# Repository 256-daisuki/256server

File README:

# 256server

### Welcome to 2^8 Server!! 👋
Here is the repository of the server operated by @256_daisuki.

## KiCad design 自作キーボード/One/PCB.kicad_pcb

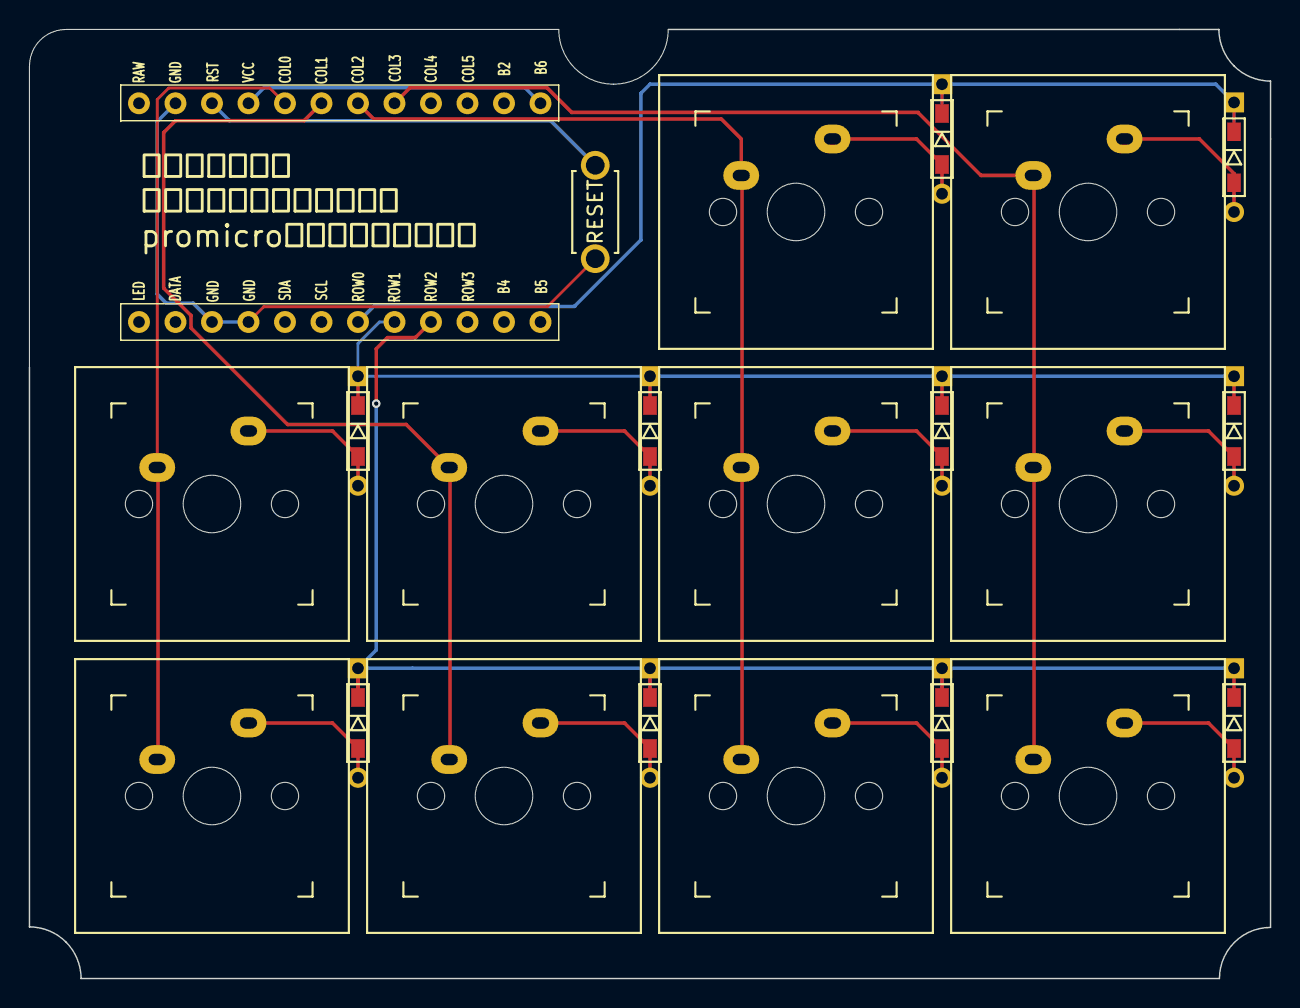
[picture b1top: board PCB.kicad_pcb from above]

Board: 2 copper layers, 86.4 x 66.0 mm, 22 parts (1 on the bottom side), 19 nets.

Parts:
D1, D2, D3, D4, D5, D6, D7, D8, D9, D10: D; D3_TH_SMD
SW1, SW2, SW3, SW4, SW5, SW6, SW7, SW8, SW9, SW10: SW_Push; CherryMX_1u
SW11: SW_Push; ResetSW_1side
U1: Micon_BLEMicroPro; ProMicro_v2_1side

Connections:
Col0: SW3.1, SW7.1, U1.20 (F4/PIN20)
Col1: SW4.1, SW8.1, U1.19 (F5/PIN19)
Col2: SW1.1, SW5.1, SW9.1, U1.18 (F6/PIN18)
Col3: SW2.1, SW6.1, SW10.1, U1.17 (F7/PIN17)
GND: SW11.2, U1.3 (GND), U1.4 (GND), U1.23 (GND)
unnamed: D1.2 (A), SW1.2
unnamed: D2.2 (A), SW2.2
unnamed: D3.2 (A), SW3.2
unnamed: D4.2 (A), SW4.2
unnamed: D5.2 (A), SW5.2
unnamed: D6.2 (A), SW6.2
unnamed: D7.2 (A), SW7.2
unnamed: D8.2 (A), SW8.2
unnamed: D9.2 (A), SW9.2
unnamed: D10.2 (A), SW10.2
Reset: SW11.1, U1.22 (RST)
Row0: D1.1 (K), D2.1 (K), U1.7 (D4/PIN7)
Row1: D3.1 (K), D4.1 (K), D5.1 (K), D6.1 (K), U1.8 (C6/PIN8)
Row2: D7.1 (K), D8.1 (K), D9.1 (K), D10.1 (K), U1.9 (D7/PIN9)

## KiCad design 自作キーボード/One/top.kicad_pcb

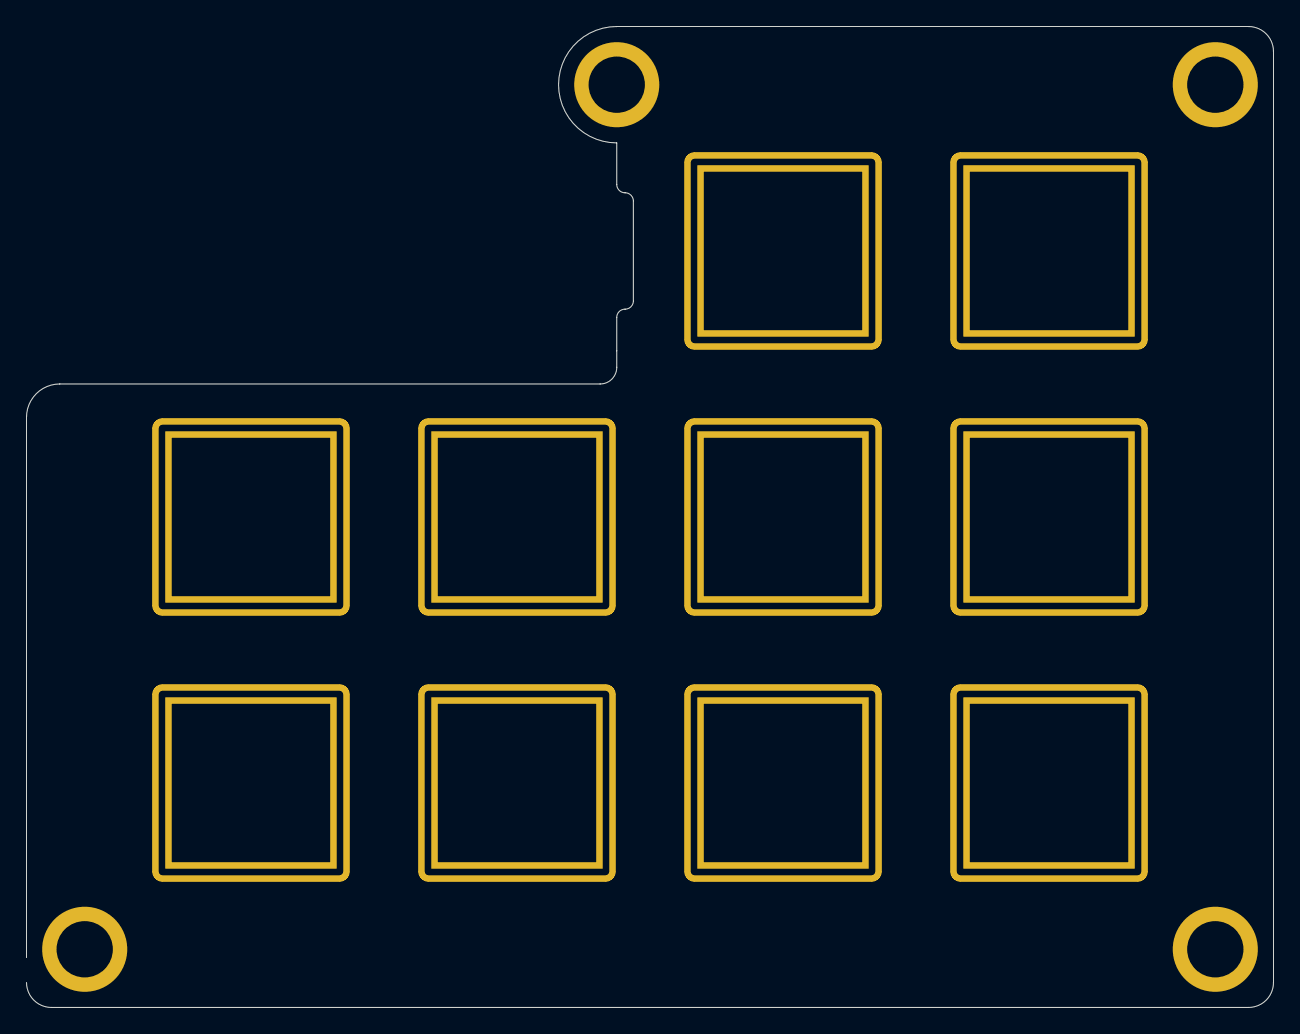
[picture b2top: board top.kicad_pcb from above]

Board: 2 copper layers, 95.3 x 74.9 mm, 14 parts (0 on the bottom side), 4 nets, no tracks yet.

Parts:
Ref**: Val**; M2_HOLE
Ref**#2, Ref**#3, Ref**#4: Val**; M2_HOLE
SW1, SW2, SW3, SW4, SW5, SW6, SW7, SW8, SW9, SW10: SW_Push; SW_Hole_TH

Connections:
Col0: SW3.1, SW7.1
Col1: SW4.1, SW8.1
Col2: SW1.1, SW5.1, SW9.1
Col3: SW2.1, SW6.1, SW10.1

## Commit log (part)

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2023-02-21 やっとシステム構築できたぁ！！！！！！！！！！！！！！！！！！
2023-02-22 どんべい
2023-02-22 ファイル移動
2023-02-23 うぇーい
2023-02-23 結構頑張ってる
2023-02-23 inaoepyikaeo
2023-02-23 色々修正
2023-02-23 banner解禁
2023-02-23 今日はもう終わり メロンパンくれよ
2023-02-24 ping入れた
2023-02-24 わたくし、メロンパンが大好きなの
2023-02-25 昨日コミットしてなかった うんち
2023-02-25 とりあえず
2023-02-26 AIにエンジニアは殺される 私はAIにアバダケダブラをされて殺される。
2023-02-27 スマホ大体対応
2023-03-06 キャッシュがあっても無くても大体同じやんす たすけてヤンス
2023-03-07 色々頑張ってます。
2023-03-08 404って大事だと思ったんだ
2023-03-08 404完成
2023-03-09 aisitenu
2023-03-12 あいえかおい
2023-03-12 bbs作った
2023-03-13 ばななおいちい
2023-03-13 お腹空いたからねるわ
2023-03-13 AIにコードぐちゃぐちゃにされたわ 怒っていません
2023-03-18 aaaa
2023-03-24 yaer
2023-03-27 onimai o
2023-03-27 PCの容量無くなった
2023-03-27 iaoeiioank
2023-03-28 疲れたんだけど 給料出ないってマジ？
2023-03-28 お兄ちゃんはCSS
2023-03-30 し まで終わったわ
2023-03-31 なんかコード消えてる
2023-03-31 なんでコード白紙になったかなー
2023-03-31 これでコードのバックアップ大丈夫だろ（フラグ）
2023-03-31 バックアップ取れてなかったなでこd
2023-03-31 ま また完成
2023-03-31 後少しで完成だ
2023-03-31 大体完成
2023-03-31 大まか完成
2023-04-24 PC復活
2023-04-30 自作キーボードに手を出すそうです。
2023-04-30 ファイルの追加と削除、今からコード書いてくよ
2023-04-30 今日はもうコード書きたくないかもしれないのかもしれないのかもしれない
2023-05-02 本番に合わせた それだけよ コミットタイプミスでキモっとになったｗ
2023-05-06 よくわかんない
2023-05-07 unchi
2023-05-11 おにぎり食べすぎておなか痛い
2023-05-11 つかれたつかれたつかれたつかれたつかれたつかれたつかれたつかれた
2023-05-11 ﾊﾗﾍｯﾀ
2023-05-11 ファイルの移動！！！！！うぇええええええええええい いｗｗｗｗｗｗｗｗｗｗｗｗｗｗ あしたあした ねねね 明日Ｅ えええええＩ？ なんだって！
2023-05-11 ファイル移動なう
2023-05-11 大幅にさくじょーーーーーーーーーーーーーーーーーーーーーーーーーー
2023-05-12 とりあえず今日のコミット
2023-05-12 つかれた
2023-05-12 とりあえずセーブ
2023-05-13 疲れました
2023-05-14 こみっとっと
2023-05-14 CSSムズイ
2023-05-15 今日は何しようかなー
2023-05-17 aaaaaaa
2023-05-17 タイマー製作なう
2023-05-17 save
2023-05-17 今日、頑張ってます。
2023-05-17 あとすこしー
2023-05-17 winでしか確認してないﾖ
2023-05-17 久しぶりに集中したわ
2023-05-18 ﾁｶﾚﾀ
2023-05-30 192.168.100.ウルズニャー
2023-06-04 test
2023-06-06 改行バグ修正
2023-06-08 裏で働いてます。
2023-06-13 ganbattayo
2023-06-14 意味が分かんない
2023-06-16 サーバー移行につき更新
2023-06-16 proxyサーバーのファイル追加やで！
2023-06-18 ipアドレスの変更。
2023-06-18 bbsバックアップ
2023-06-18 php練習
2023-06-19 昨日やったやつ
2023-06-20 アクセスカウンターのサーバー変更
2023-06-28 こんど徳陽に
2023-06-30 ヘッダー君をお直し（作りなおし）をするで
2023-06-30 日が変わった！！！！！アイコン描いた人が消えた！！！！！
2023-06-30 PC版完成
2023-06-30 なんとなくスマホ対応 やったぜ
2023-07-01 BBS荒らされたんだが ばーか
2023-07-01 なんかおかしい
2023-07-01 CSSと紛争しています。
2023-07-02 なんでスマホなんてあるんだよ
2023-07-02 鯖を追加しました
2023-07-09 proxyあたりの修正
2023-07-11 アクセスログ追加
2023-07-14 同盟バナー追加
2023-07-16 ちょびっと変更
2023-07-18 なにしたか忘れちゃった
2023-07-19 bbsのルールを追加
2023-07-19 ファイル削除
2023-07-19 ヘッダーの改修
2023-07-19 なんかあった
2023-07-19 不必要なファイルの削除
2023-07-19 ルール追加のため、リンクを追加
2023-07-19 忘れてたところ
2023-07-20 フッターの改修
2023-07-20 使われてないファイル削除
2023-07-20 軽微な修正
2023-07-21 コメントアウトしたままだった
2023-07-22 ちょびｔｔｔｔｔｔっとだけ修正 見る価値無し
2023-07-23 変更し忘れ C言語もやりたいよ
2023-07-24 著作権はTwitter社が持ってます
2023-07-24 256server.tk
2023-07-25 微微微微微微微微微微微微微微微微微微微微調整
2023-07-26 最後とを統一
2023-07-27 ずっとあったバグを直した
2023-07-28 コード拝借と直し
2023-07-31 bbsのほうでいろいろやってその副産物
2023-08-01 設定変更
2023-08-03 ヤドン爆してる人を特定したい
2023-08-03 犬大好き
2023-08-04 消し忘れとちょっとだけ変更
2023-08-06 BBSのリンク変更
2023-08-07 フッターにリンク追加した
2023-08-09 やる気の突然消失
2023-08-13 くそどうでもいい
2023-08-15 ちょいっとね
2023-08-18 まあちょびっと
2023-08-18 discordBOTに手を出しました
2023-08-19 discord
2023-08-19 昨日描いたコード
2023-08-20 シェル使えるようになった
2023-08-24 これでいいんか？
2023-08-24 だから私はXperia
2023-08-24 こんにちは
2023-08-24 ばななーず
2023-08-24 はいはいはいはいはいはいはいはいは
2023-08-24 Update nginx.conf
    どうですか！！！
2023-08-25 めんどい
2023-08-27 夏休み 最初はずっとコミットしてたのに いつのまにか まちまちに
2023-08-27 じゃじゃじゃじゃじゃあーん
2023-08-30 cssでリコ君を書くことになりました
2023-08-30 jsでアニキャラ！？
2023-09-02 大人の事情
2023-09-02 rustrust
2023-09-06 画像保存機能追加
2023-09-06 astkaoeniksteankistaornopystkeyaxoioe
2023-09-06 もうやりたくない
2023-09-06 とりあえず終了！！！！！！！！！！！！！！！！！！！！！
2023-09-08 コミットメント
2023-09-09 ちょっとね
2023-09-09 気のせい
2023-09-09 ぬぬぬぬぬぬぬぬぬぬぬぬぬぬ
2023-09-09 connectの成功
2023-09-09 コードの簡素化
2023-09-12 めちゃめちゃファイル移動
2023-09-13 ゴミは削除
2023-09-13 npmインストールらしい
2023-09-16 なんかいろいろやったっぽいよ
2023-09-16 ぬぬぬぬぬぬぬぬぬぬぬぬぬぬぬぬぬぬぬぬぬぬぬぬぬぬぬぬぬぬぬぬぬぬぬぬぬ
2023-09-28 溜まってた
2023-10-04 なにこれぇぇ
2023-10-05 3dモデルのテスト
2023-10-05 なんか惜しい
2023-10-05 くりくり動かせるようになった 面白い 楽しい
2023-10-05 もう無理疲れたお休みしたいがさっき寝たのでこのまま頑張る～～おｐ
2023-10-07 add reciprocal link
2023-10-07 index.html を更新
2023-10-22 文の追加
2023-10-22 障害情報
2023-11-11 最近コード書く気起きないってかサーバーの管理で掛けない
2023-11-25 abayn
2023-12-02 コミットできてないらしい
2023-12-02 コミットテスト
2023-12-04 何か直したんだと思う 昨日のことだから忘れた
2023-12-07 あうあうああああああああああああ
2023-12-16 add:commit test
2023-12-16 add:memo.mdの作成
2023-12-17 remove:タスク管理ソフト用の別のリポジトリを立てることに決定
2023-12-31 あけおめ
2023-12-31 なんか消えてたんだが
2023-12-31 消えてたなんか
2024-01-03 googleコマンドが死んでたわ（笑）
2024-02-14 emoji変えた クソ久しぶりのコミットっすね
2024-03-23 aaaaaa
2024-03-23 cpuコア数取得
2024-03-23 とりあえず鯖に突っ込んだ
2024-03-23 pingを打ちます
2024-03-23 破棄(2回目)
2024-03-23 いろいろ
2024-04-24 aaaaaaaaaaaaa
2024-04-24 とりあえず動いた
2024-06-09 sakujo
2024-06-19 uaaaaa
2024-09-07 aaaaa
2024-09-07 トップページ本文の変更
2024-09-07 メモアプリのデザインの追加
2024-09-07 細かな修正を大量に
2024-09-07 追加したコマンドに合わせてhelpの更新
2024-09-08 エラーコード専用ページの作成
2024-09-08 全体的に微かな修正
2024-09-10 フッター調整
2024-09-10 リンクの更新
2024-09-11 本文の追加
2024-09-12 相互リンクは新しいタブで開くようにした
2024-09-16 不要となったファイルの削除
2024-10-02 labの追加
2024-10-03 メンバーの追加
2024-10-03 リンクミスの修正
2024-10-03 強調をつける場所ミスってた
2024-10-05 プライバシーポリシーの追加
2024-10-05 オプション作った
2024-12-19 VScode再起動したらなんか出てた
2024-12-19 アホなのでパッケージ事コミットします これどうやって消すんですか
2024-12-19 今度作るから消す
2024-12-19 markdown
2025-01-24 画像の追加
2025-01-25 表示の追加
2025-02-11 なんかCD使えなくなるから
2025-03-01 tuika
2025-03-16 カスカスカスカスカスカスカスカスカスカスカスカスカスカスカスカスカスカスカスカスカスカスカスカスカスカスカスカスカスカスカスカスカスカスカスカスカスカスカスカスカスカスカスカスカスカスカスカスカスカスカスカスカスカスカスカスカスカスカスカスカスカスカスカスカスカスカスカスカスカスカスカスカスカスカスカスカスカスカスカスカスカス
2025-03-22 DISCORDBOTに機能追加
2025-03-22 相互リンク追加
2025-03-30 動作の高速化
2025-03-30 使わない機能の追加
2025-04-09 たぶん相互リンクを追加したのかな？
2025-04-09 画像をいつく保存したかわかるやつ
2025-04-13 ファイル移動1
2025-04-13 相互リンクのリンク変更
2025-04-13 なぜか消えていた機能の復活
2025-04-13 作り直した部分
2025-04-13 ファイル移動、だと思う
2025-04-13 あああああああああああああああああああああああ
2025-04-13 blogの構造を大幅に変更しました
2025-04-29 t3traさんの相互リンク追加
2025-05-13 fxtwitterで超高速化しました
2025-05-13 ブログ書きました
2025-05-16 ファイルネーム変更
2025-05-21 discordbotを紹介
2025-06-01 ランダムな画像のアレ
2025-10-04 楽しくないことだけ
2025-10-07 相互リンクの追加
2025-10-07 スマートフォン版, ダークモードの時に背景の凛世とタイトルの文字が被るので避けるようにした & スマホ, PCの判定の境界の変更
2025-10-07 OGPのコメントを変更
2026-01-18 discordbot 動画とかテキストとか対応してjson保存するようにした
2026-01-18 256serverなんかいろいろ
2026-01-18 相互リンクの編集
2026-01-18 helpの修正 filecountのカンマ追加
2026-01-18 256botの記述の追加
2026-01-18 256bot紹介の記述の修正
2026-03-12 blog
2026-03-12 インデックスの削除, 戻るボタンの追加
2026-03-12 少し調整 ブログ用メイン style.css: sの色のみ blog.css: フォントの指定、色の指定
2026-03-12 bot紹介用ページ 本文編集
2026-03-14 queueの追加 見つけたツイートすべてをアーカイブするバーサーカーにした
2026-03-14 フォントの変更
2026-03-30 bot説明 簡略化
2026-03-30 あああああああああああ
